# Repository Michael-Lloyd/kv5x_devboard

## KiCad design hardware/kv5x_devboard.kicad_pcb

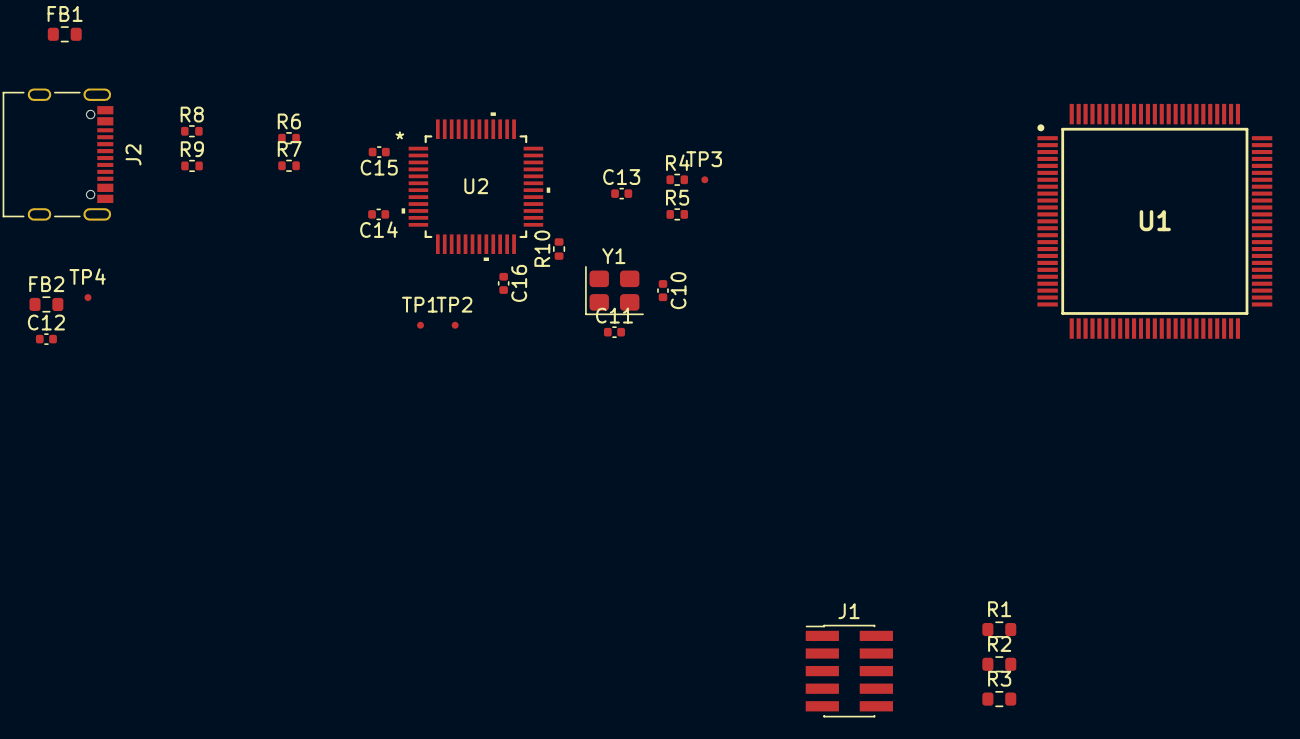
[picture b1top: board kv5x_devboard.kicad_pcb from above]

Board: 2 copper layers, 28 parts (0 on the bottom side), 22 nets, no tracks yet.

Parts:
C10, C11: 15pF; C_0402_1005Metric
C12: 1uF; C_0402_1005Metric
C13, C14, C15, C16: 0.1uF; C_0402_1005Metric
FB1, FB2: 330R; R_0603_1608Metric
J1: JTAG/SWD Connector; PinHeader_2x05_P1.27mm_Vertical_SMD
J2: USB_C_Receptacle_USB2.0_16P; USB_C_Receptacle_Palconn_UTC16-G
R1: 10K; R_0603_1608Metric
R2, R3: 10K/DNP; R_0603_1608Metric
R4: 4.7k; R_0402_1005Metric
R5: 10k; R_0402_1005Metric
R6, R7: 33R; R_0402_1005Metric
R8, R9: 5.1k; R_0402_1005Metric
R10: 1M; R_0402_1005Metric
TP1, TP2, TP3, TP4: TestPoint; TestPoint_Pad_D0.5mm
U1: MKV56F1M0VLL24
U2: MK20DX128VLF5
Y1: ECS-80-12-33-JGN-TR; Crystal_SMD_3225-4Pin_3.2x2.5mm

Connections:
+3.3V: C14.1, C15.1, C16.1, U2.1 (VDD1), U2.6 (VREGIN), U2.9 (VDDA), U2.10 (VREFH), U2.16 (VBAT), U2.22 (VDD2)
/USB interface/SDA_USB_DM: R7.2, U2.4 (USB0_DM)
/USB interface/SDA_USB_DP: R6.2, U2.3 (USB0_DP)
/USB interface/SDA_XTAL_IN: C11.1, R10.2, U2.24 (EXTAL0/PTA18/FTM0_FLT2/FTM_CLKIN0), Y1.1
/USB interface/SDA_XTAL_OUT: C10.1, R10.1, U2.25 (XTAL0/PTA19/FTM1_FLT0/FTM_CLKIN1/LPTMR0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), Y1.3
/USB interface/SDA_~RESET: C13.1, R4.2, R5.1, TP3.1, U2.26 (~RESET)
/USB interface/TC_EXTAL_TP: TP1.1, U2.15 (EXTAL32)
/USB interface/TC_XTAL_TP: TP2.1, U2.14 (XTAL32)
/USB interface/USB_D+: J2.A6 (D+), J2.B6 (D+), R6.1
/USB interface/USB_D-: J2.A7 (D-), J2.B7 (D-), R7.1
/USB interface/USB_SHIELD: FB1.1, J2.S1 (SHIELD)
/USB interface/USB_VBUS: FB2.1, J2.A4 (VBUS), J2.A9 (VBUS), J2.B4 (VBUS), J2.B9 (VBUS)
GND: C10.2, C11.2, C12.2, C13.2, C14.2, C15.2, C16.2, FB1.2, J1.3, J1.5, J1.9, J2.A1 (GND), J2.A12 (GND), J2.B1 (GND), J2.B12 (GND), R3.1, R5.2, R8.2, R9.2, U1.9 (VSS_1), U1.24 (VREFL), U1.25 (VSSA), U1.29 (VSS_2), U1.41 (VSS_3), U1.49 (VSS_4), U1.60 (VSS_5), U1.74 (VSS_6), U1.88 (VSS_7), U2.2 (VSS1), U2.11 (VREFL), U2.12 (VSSA), U2.23 (VSS2), Y1.2, Y1.4
KV5x_SWCLK/TCK: J1.4, R3.2, U1.34 (PTA0)
KV5x_SWDIO/TMS: J1.2, R1.2, U1.37 (PTA3)
KV5x_SWO/TDO: J1.6, R2.2, U1.36 (PTA2)
KV5x_TDI: J1.8, U1.35 (PTA1)
KV5x_~RESET: J1.10, U1.52 (RESET_B)
unnamed: J2.A5 (CC1), R8.1
unnamed: J2.B5 (CC2), R9.1
VBUS: C12.1, FB2.2, R4.1, TP4.1
VDD_MCU: J1.1, R1.1, R2.1, U1.8 (VDD_1), U1.22 (VDDA), U1.23 (VREFH), U1.30 (VDD_2), U1.40 (VDD_3), U1.48 (VDD_4), U1.61 (VDD_5), U1.75 (VDD_6), U1.89 (VDD_7)

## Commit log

2025-06-30 Project creation, first symbol/footprint/model
2025-06-30 JTAG/SWD connector and pinouts
2025-06-30 Removed unused schematic file
2025-06-30 re-added USB interface because I realized I needed it
2025-07-03 USB interface half done
